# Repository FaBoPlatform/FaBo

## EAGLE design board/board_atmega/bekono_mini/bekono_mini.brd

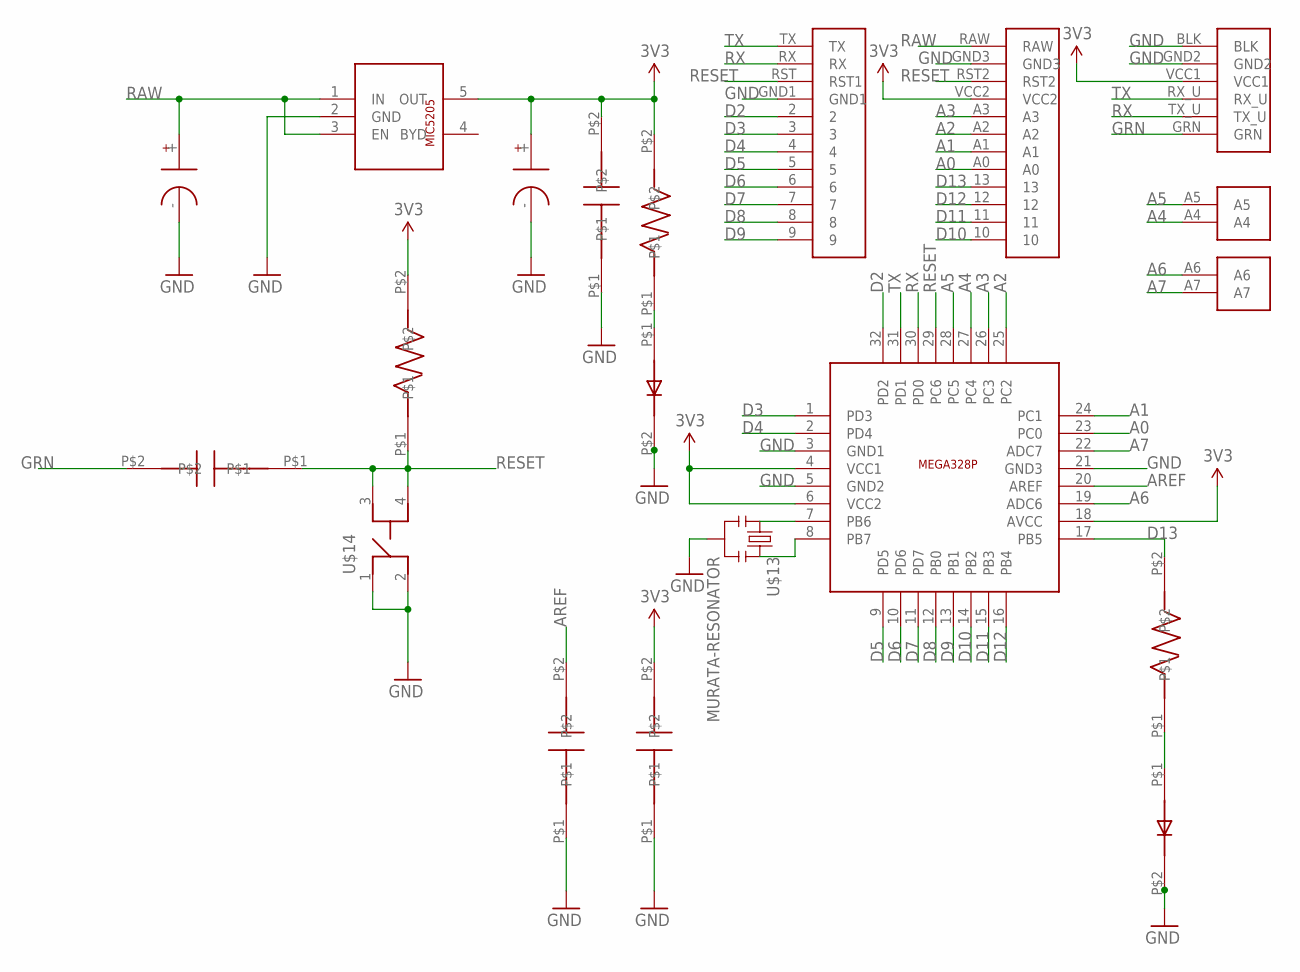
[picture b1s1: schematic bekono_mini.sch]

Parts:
U$1: ARDUIN-MINIPRO-BASE; ARDUINO-MINIPRO-BASE
U$2: MICREL-MIC5205
U$3, U$4: TANTALUM-CAPACITOR-1206
U$5, U$11, U$12, U$16: CAPACITOR-0603; 0603
U$6, U$9, U$15: RESISTOR-0603; 0603
U$7, U$10: LED-0603; 0603
U$8: ATMEL-MEGA328P; ATNEL-MEGA328P
U$13: MURATA-RESONATOR
U$14: SWITCH-LS6J2M-T

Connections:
3V3: U$1.VCC1, U$1.VCC2, U$2.5 (OUT), U$4.+, U$5.P$2, U$6.P$2, U$8.4 (VCC1), U$8.6 (VCC2), U$8.18 (AVCC), U$11.P$2, U$15.P$2
A0: U$1.A0, U$8.23 (PC0)
A1: U$1.A1, U$8.24 (PC1)
A2: U$1.A2, U$8.25 (PC2)
A3: U$1.A3, U$8.26 (PC3)
A4: U$1.A4, U$8.27 (PC4)
A5: U$1.A5, U$8.28 (PC5)
A6: U$1.A6, U$8.19 (ADC6)
A7: U$1.A7, U$8.22 (ADC7)
AREF: U$8.20 (AREF), U$12.P$2
D2: U$1.2, U$8.32 (PD2)
D3: U$1.3, U$8.1 (PD3)
D4: U$1.4, U$8.2 (PD4)
D5: U$1.5, U$8.9 (PD5)
D6: U$1.6, U$8.10 (PD6)
D7: U$1.7, U$8.11 (PD7)
D8: U$1.8, U$8.12 (PB0)
D9: U$1.9, U$8.13 (PB1)
D10: U$1.10, U$8.14 (PB2)
D11: U$1.11, U$8.15 (PB3)
D12: U$1.12, U$8.16 (PB4)
D13: U$1.13, U$8.17 (PB5), U$9.P$2
GND: U$1.BLK, U$1.GND1, U$1.GND2, U$1.GND3, U$2.2 (GND), U$3.-, U$4.-, U$5.P$1, U$7.P$2, U$8.3 (GND1), U$8.5 (GND2), U$8.21 (GND3), U$10.P$2, U$11.P$1, U$12.P$1, U$13.2, U$14.1, U$14.2
GRN: U$1.GRN, U$16.P$2
unnamed: U$6.P$1, U$7.P$1
unnamed: U$8.7 (PB6), U$13.1
unnamed: U$9.P$1, U$10.P$1
unnamed: U$8.8 (PB7), U$13.3
RAW: U$1.RAW, U$2.1 (IN), U$2.3 (EN), U$3.+
RESET: U$1.RST (RST1), U$1.RST2, U$8.29 (PC6), U$14.3, U$14.4, U$15.P$1, U$16.P$1
RX: U$1.RX, U$1.TX_U, U$8.30 (PD0)
TX: U$1.RX_U, U$1.TX, U$8.31 (PD1)

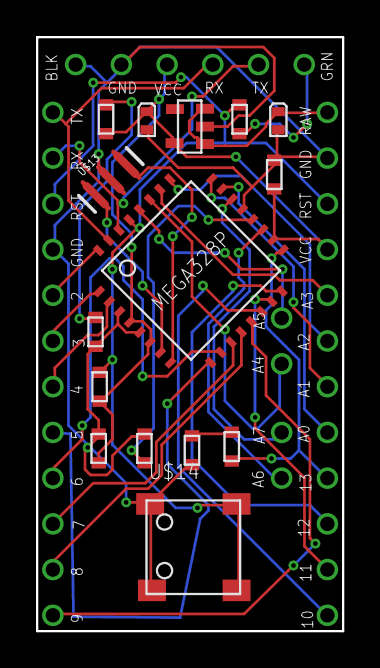
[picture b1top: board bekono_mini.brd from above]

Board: 2 copper layers, 17.0 x 33.0 mm, 16 parts (0 on the bottom side), 32 nets.

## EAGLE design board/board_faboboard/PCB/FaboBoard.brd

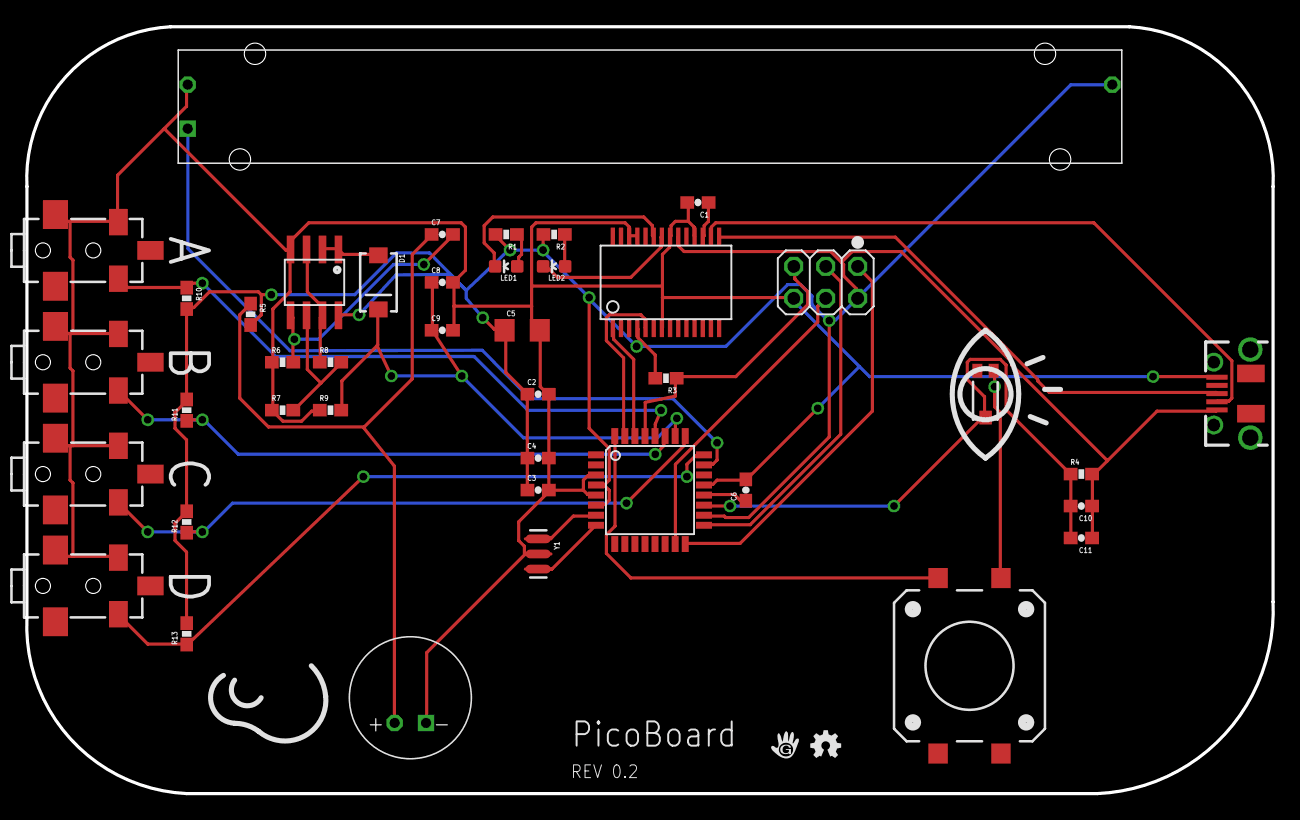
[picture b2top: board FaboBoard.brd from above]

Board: 2 copper layers, 99.1 x 61.0 mm, 43 parts (0 on the bottom side), 31 nets.

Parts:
C1, C2, C3, C4, C6, C7, C8, C9, C11: 0.1uF; EIA0603-CAP
C5: 10uF; EIA1206
C10: 0.22uF; EIA0603-CAP
D1: MBRA140; DIODE-SMA
JP1: AVR Prog.; 2X03
JPA: 2.5MM; STEREOJACK_2.5MM_SMD
JPB: 2.5MM; STEREOJACK_2.5MM_SMD
JPC: 2.5MM; STEREOJACK_2.5MM_SMD
JPD: 2.5MM; STEREOJACK_2.5MM_SMD
LED1: Red; EIA0603-LED
LED2: Green; EIA0603-LED
R1, R2: 1k; EIA0603-RES
R3, R5, R6, R10, R11, R12, R13: 10k; EIA0603-RES
R4, R8, R9: 100k; EIA0603-RES
R7: 2.2k; EIA0603-RES
R14: SLIDER; SLIDER_60MM
S1: TACT-SMD-12MM-TL3300CF160Q
U1: FT232RL; SSOP28
U2: ATMEGA328P-AU; TQFP-32-08
U7: TEMT6000
U8: LMV358; SO8-OP
U9: MIC9.7MM; MIC-ECM
U$2: LOGO_GCLUE
U$3: LOGO_OSHW_S
USB1: USBMICRO_SMD; USB_B_MICRO
Y1: 16MHz; RESONATOR_SMD

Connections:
3V3: C1.1, U1.17
5V: C2.1, C3.1, C4.1, C5.1, C10.1, C11.1, JP1.2, R1.2, R2.2, R3.2, R4.2, R5.2, R10.2, R11.2, R12.2, R13.2, R14.3, U1.4, U1.20, U2.4, U2.6, U2.18, U8.8, USB1.VBUS
GND: C1.2, C2.2, C3.2, C4.2, C5.2, C6.2, C8.2, C9.2, JP1.6, JPA.1, JPA.5, JPB.1, JPB.5, JPC.1, JPC.5, JPD.1, JPD.5, R6.1, R7.1, R9.1, R14.1, S1.4, U1.7, U1.18, U1.21, U1.25, U1.26, U2.3, U2.5, U2.21, U7.EMITTER, U8.4, U9.-, USB1.GND, Y1.2
LIGHT: C10.2, C11.2, R4.1, U2.19, U7.COLLECTOR
MISO: JP1.1, U2.16
MOSI: JP1.4, U2.15
unnamed: LED1.A, R1.1
unnamed: LED2.A, R2.1
unnamed: R7.2, R8.2, U8.6
unnamed: U2.7, Y1.1
unnamed: U2.8, Y1.3
unnamed: C6.1, U2.20
unnamed: S1.2, U2.32
unnamed: C7.1, R5.1, U9.+
unnamed: R14.2, U2.23
unnamed: C7.2, R6.2, U8.5
unnamed: D1.A, U8.1, U8.2
unnamed: R8.1, U8.3, U8.7
RA: JPA.4, R10.1, U2.28
RB: JPB.4, R11.1, U2.27
RC: JPC.4, R12.1, U2.25
RD: JPD.4, R13.1, U2.24
RES: JP1.5, R3.1, U2.29
RXI: U1.1, U2.30
RXLED: LED2.C, U1.22
SCK: JP1.3, U2.17
SOUND: C8.1, C9.1, D1.C, R9.2, U2.26
TXLED: LED1.C, U1.23
TXO: U1.5, U2.31
USB_D+: U1.15, USB1.D+
USB_D-: U1.16, USB1.D-

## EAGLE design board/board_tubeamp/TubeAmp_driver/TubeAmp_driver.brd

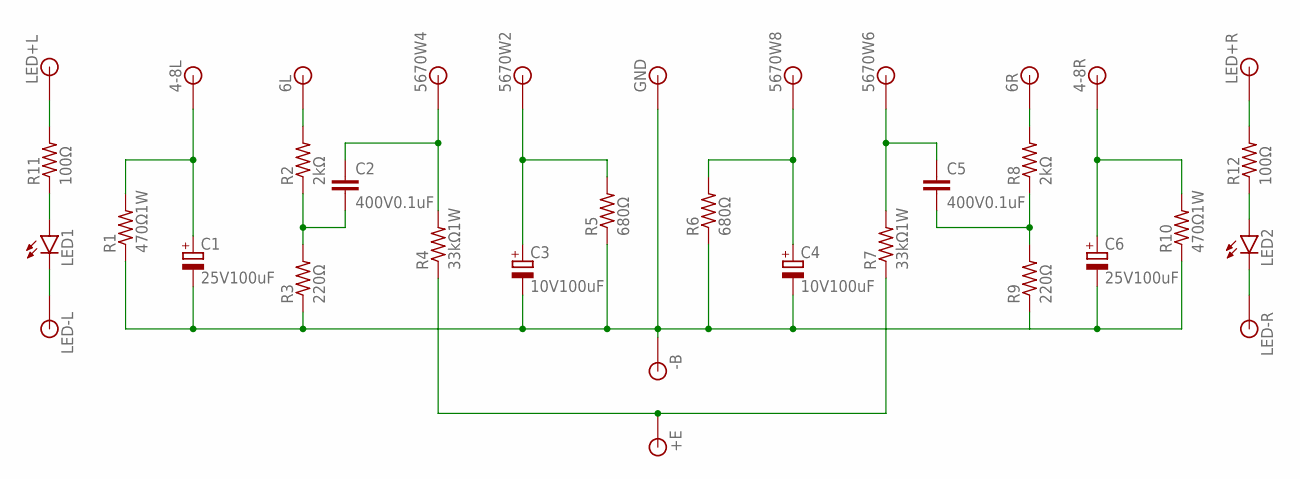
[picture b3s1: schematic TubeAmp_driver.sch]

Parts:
4-8L, 4-8R, 6L, 6R, 5670W2, 5670W4, 5670W6, 5670W8: PIN-1X11.2MM; PIN-1X1_1.2MM
+E: PIN-1X11.2MM; PIN-1X1_1.2MM
-B: PIN-1X11.2MM; PIN-1X1_1.2MM
C1, C6: 25V100uF; CPOL25_65
C2, C5: 400V0.1uF; C125_63X155
C3, C4: 10V100uF; CPOL25_65
GND: PIN-1X11.2MM; PIN-1X1_1.2MM
LED1, LED2: LED-3MM
LED+L: PIN-1X11.2MM; PIN-1X1_1.2MM
LED+R: PIN-1X11.2MM; PIN-1X1_1.2MM
LED-L: PIN-1X11.2MM; PIN-1X1_1.2MM
LED-R: PIN-1X11.2MM; PIN-1X1_1.2MM
R1, R10: 470Ω1W; RESISTOR_1W
R2, R8: 2kΩ; RESISTOR_1/4W
R3, R9: 220Ω; RESISTOR_1/4W
R4, R7: 33kΩ1W; RESISTOR_1W
R5, R6: 680Ω; RESISTOR_1/4W
R11, R12: 100Ω; RESISTOR_1/4W

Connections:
4-8L: 4-8L.1, C1.+, R1.2
4-8R: 4-8R.1, C6.+, R10.2
6L: 6L.1, R2.2
6R: 6R.1, R8.2
5670W2: 5670W2.1, C3.+, R5.2
5670W4: 5670W4.1, C2.1, R4.2
5670W6: 5670W6.1, C5.1, R7.2
5670W8: 5670W8.1, C4.+, R6.2
+E: +E.1, R4.1, R7.1
-B: -B.1, C1.-, C3.-, C4.-, C6.-, GND.1, R1.1, R3.1, R5.1, R6.1, R9.1, R10.1
LED+L: LED+L.1, R11.2
LED+R: LED+R.1, R12.2
LED-L: LED1.K (C), LED-L.1
LED-R: LED2.K (C), LED-R.1
unnamed: C2.2, R2.1, R3.2
unnamed: LED1.A, R11.1
unnamed: LED2.A, R12.1
unnamed: C5.2, R8.1, R9.2

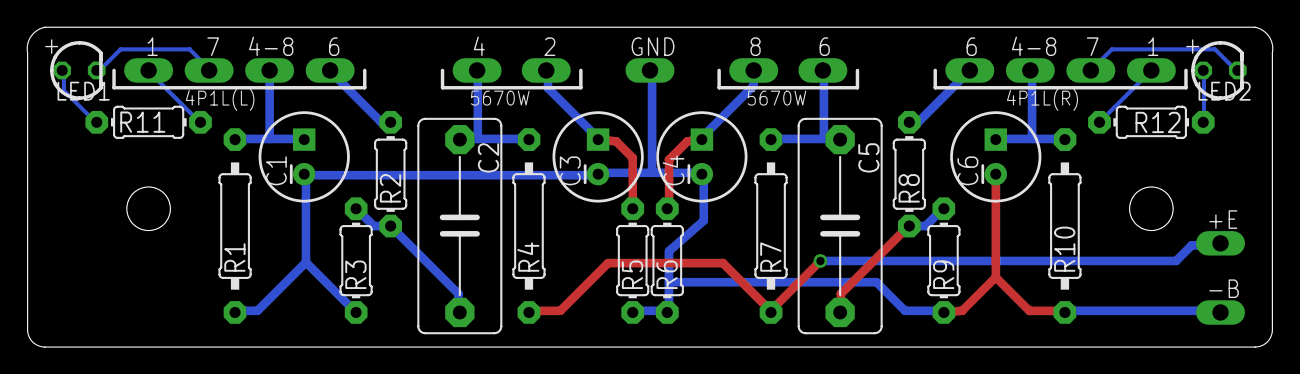
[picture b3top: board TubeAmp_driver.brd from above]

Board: 2 copper layers, 91.5 x 23.5 mm, 35 parts (0 on the bottom side), 18 nets.

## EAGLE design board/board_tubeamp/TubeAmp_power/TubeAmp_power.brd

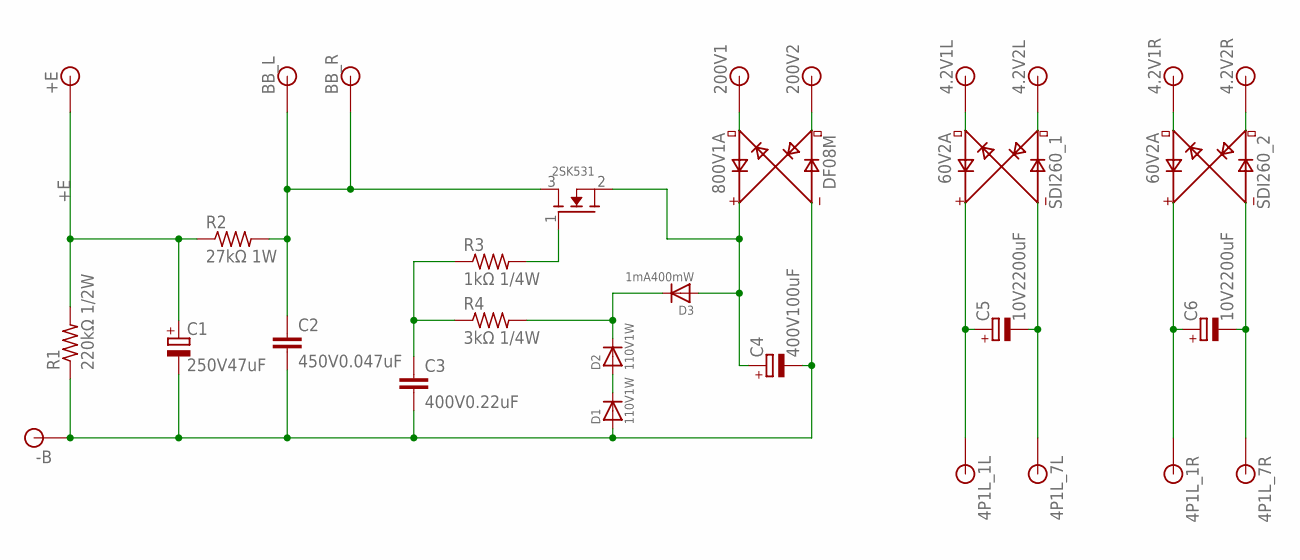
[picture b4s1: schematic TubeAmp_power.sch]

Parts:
2SK531: MOSFET_N
4.2V1L, 4.2V1R, 4.2V2L, 4.2V2R, 4P1L_1L, 4P1L_1R, 4P1L_7L, 4P1L_7R, 200V1, 200V2: PIN-1X11.2MM; PIN-1X1_1.2MM
+E: PIN-1X11.2MM; PIN-1X1_1.2MM
-B: PIN-1X11.2MM; PIN-1X1_1.2MM
BB_L: PIN-1X11.2MM; PIN-1X1_1.2MM
BB_R: PIN-1X11.2MM; PIN-1X1_1.2MM
C1: 250V47uF; CPOL50_90
C2: 450V0.047uF; C150_63X200
C3: 400V0.22uF; C100_63X130
C4: 400V100uF; CPOL75_150
C5, C6: 10V2200uF; CPOL50_90
D1, D2: 110V1W; DIODE_63
D3: 1mA400mW; DIODE_63
DF08M: 800V1A; RECTIFIER
R1: 220kΩ 1/2W; RESISTOR_1/2W
R2: 27kΩ 1W; RESISTOR_1W
R3: 1kΩ 1/4W; RESISTOR_1/4W
R4: 3kΩ 1/4W; RESISTOR_1/4W
SDI260_1, SDI260_2: 60V2A; RECTIFIER

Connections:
4.2V1L: 4.2V1L.1, SDI260_1.AC2
4.2V1R: 4.2V1R.1, SDI260_2.AC2
4.2V2L: 4.2V2L.1, SDI260_1.AC1
4.2V2R: 4.2V2R.1, SDI260_2.AC1
4P1L_1L: 4P1L_1L.1, C5.+, SDI260_1.+
4P1L_1R: 4P1L_1R.1, C6.+, SDI260_2.+
4P1L_7L: 4P1L_7L.1, C5.-, SDI260_1.-
4P1L_7R: 4P1L_7R.1, C6.-, SDI260_2.-
200V1: 200V1.1, DF08M.AC2
200V2: 200V2.1, DF08M.AC1
+E: +E.1, C1.+, R1.2, R2.1
BB: 2SK531.3 (D), BB_L.1, BB_R.1, C2.1, R2.2
GND: -B.1, C1.-, C2.2, C3.2, C4.-, D1.A, DF08M.-, R1.1
unnamed: 2SK531.1 (G), R3.2
unnamed: 2SK531.2 (S), C4.+, D3.A, DF08M.+
unnamed: C3.1, R3.1, R4.1
unnamed: D2.K, D3.K, R4.2
unnamed: D1.K, D2.A

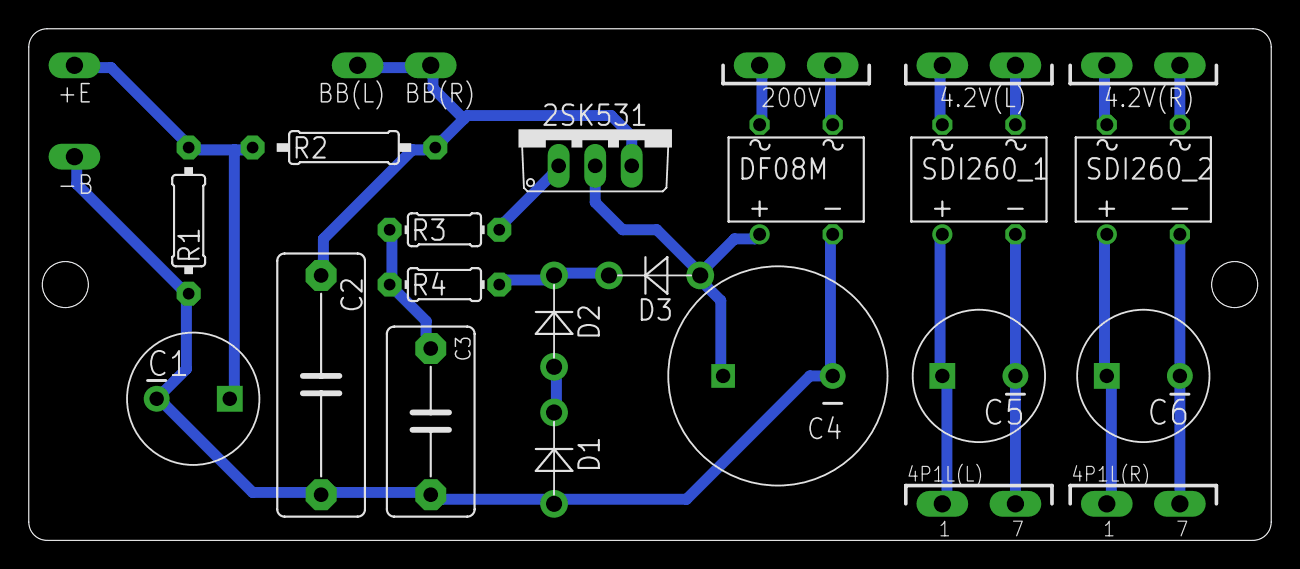
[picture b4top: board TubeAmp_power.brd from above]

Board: 2 copper layers, 86.4 x 35.6 mm, 31 parts (1 on the bottom side), 18 nets.

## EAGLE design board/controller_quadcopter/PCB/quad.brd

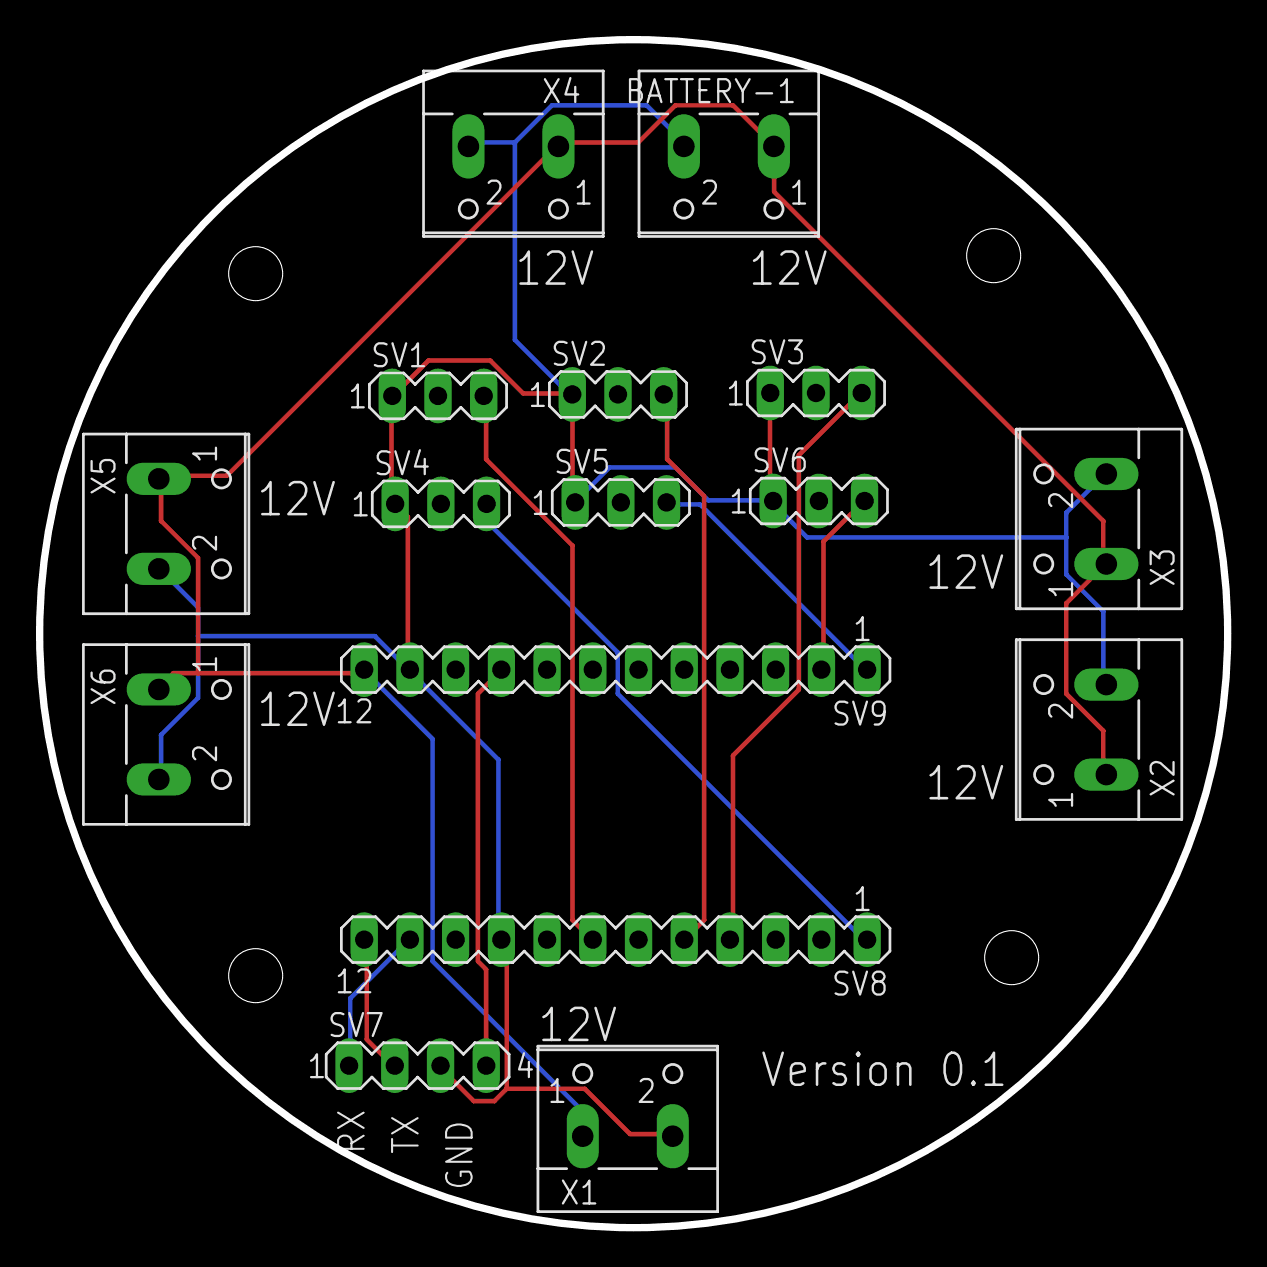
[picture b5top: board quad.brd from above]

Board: 2 copper layers, 66.0 x 66.0 mm, 16 parts (0 on the bottom side), 11 nets.

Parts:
BATTERY-1: W237-102
SV1, SV2, SV3, SV4, SV5, SV6: MA03-1
SV7: MA04-1
SV8, SV9: MA12-1
X1, X2, X3, X4, X5, X6: W237-102

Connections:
+5V: SV7.4, SV9.9
+12V: BATTERY-1.1, SV9.12, X1.1, X2.1, X3.1, X4.1, X5.1, X6.1
GND: BATTERY-1.2, SV1.1, SV2.1, SV3.1, SV4.1, SV5.1, SV6.1, SV7.3, SV8.9, SV9.11, X1.2, X2.2, X3.2, X4.2, X5.2, X6.2
M1: SV1.3, SV8.7
M2: SV2.3, SV8.5
M3: SV3.3, SV8.4
M4: SV4.3, SV8.1
M5: SV5.3, SV9.1
M6: SV6.3, SV9.2
RX: SV7.1, SV8.11
TX: SV7.2, SV8.12

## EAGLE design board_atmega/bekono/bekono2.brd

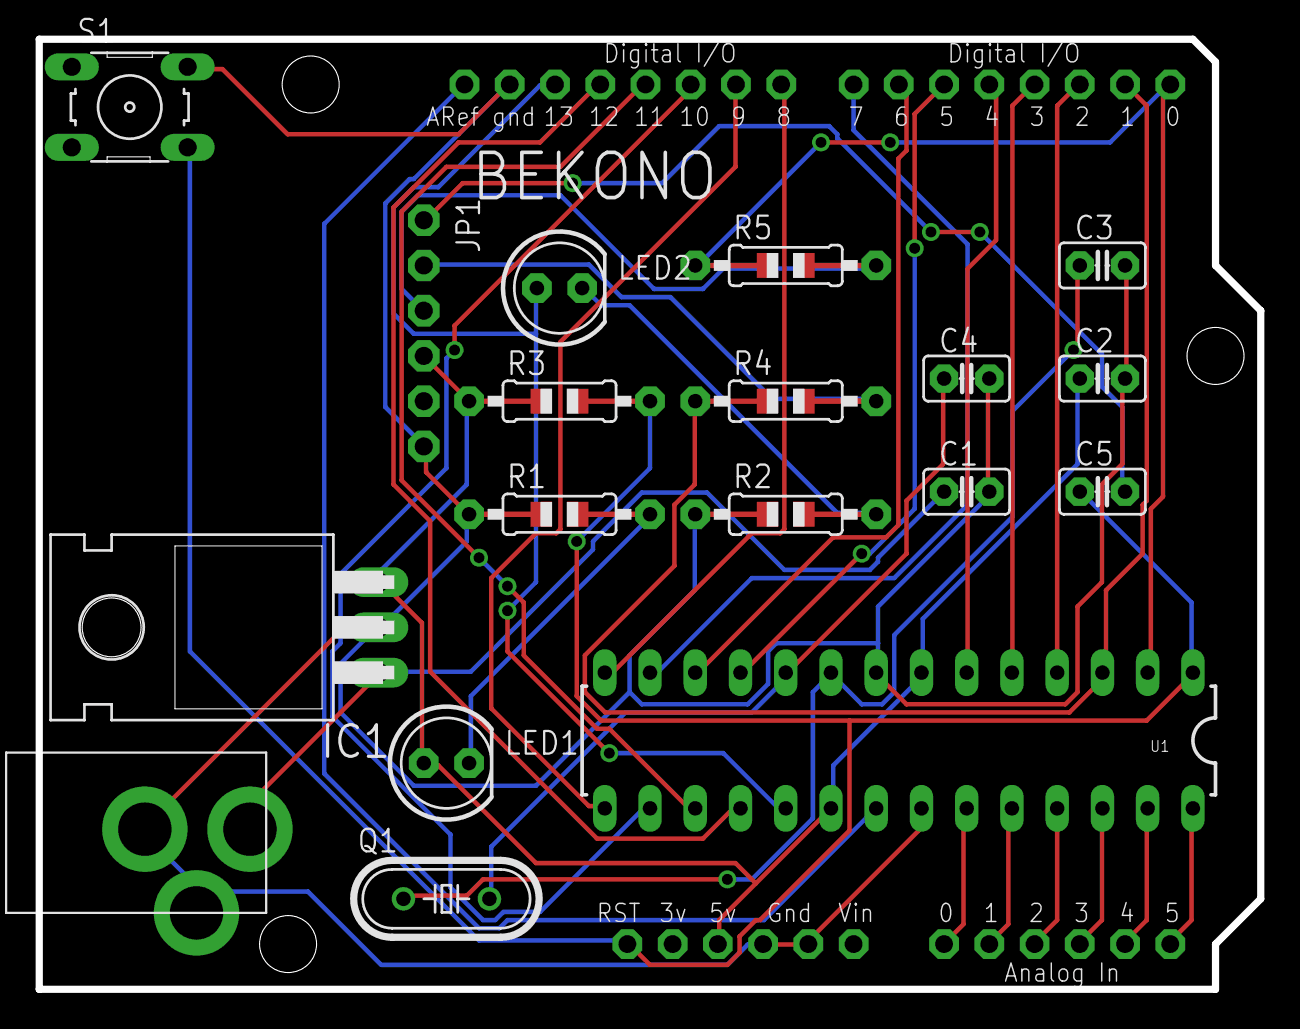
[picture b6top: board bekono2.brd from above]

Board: 2 copper layers, 68.6 x 53.3 mm, 19 parts (0 on the bottom side), 32 nets.

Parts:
C1: 0.1uf; C2.5-2
C2: 0.33uf; C2.5-2
C3, C4: 33pf; C2.5-2
C5: 1uf; C2.5-2
IC1: 7805T; TO220H
JP1: 1X06-CLEANBIG
LED1, LED2: LED5MM
Q1: HC49/S
R1, R2: 330; 0805-THM
R3: 10K; 0805-THM
R4, R5: 1K; 0805-THM
S1: B3F-10XX
U1: ATMEGA328P_PDIP; DIL28-3
U$1: ARDUINO-BPLACE
U$2: 2.1MMJACKTHM; PJ-102A

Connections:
+5V: C2.1, IC1.3, JP1.4, LED1.A, R3.1, U1.7, U1.20, U$1.5V
AREF: U1.21, U$1.AREF
GND: C1.2, C2.2, C3.2, C4.2, IC1.2, JP1.6, R1.1, R2.1, S1.2, U1.8, U1.22, U$1.GND, U$1.GND1, U$1.GND2, U$2.RING, U$2.RING_SW
unnamed: C1.1, IC1.1, U$2.TIP
unnamed: LED1.K, R1.2
unnamed: LED2.K, R2.2
unnamed: C5.2, JP1.1
unnamed: JP1.2, R4.2
unnamed: JP1.3, R5.2
PB0: U1.14, U$1.D8
PB1: U1.15, U$1.D9
PB2: U1.16, U$1.D10
PB3: U1.17, U$1.D11
PB4: U1.18, U$1.D12
PB5: LED2.A, U1.19, U$1.D13
PB6: C3.1, Q1.1, U1.9
PB7: C4.1, Q1.2, U1.10
PC0: U1.23, U$1.A0
PC1: U1.24, U$1.A1
PC2: U1.25, U$1.A2
PC3: U1.26, U$1.A3
PC4: U1.27, U$1.A4
PC5: U1.28, U$1.A5
PC6: C5.1, R3.2, S1.4, U1.1, U$1.RESET
PD0: R5.1, U1.2, U$1.D0
PD1: R4.1, U1.3, U$1.D1
PD2: U1.4, U$1.D2
PD3: U1.5, U$1.D3
PD4: U1.6, U$1.D4
PD5: U1.11, U$1.D5
PD6: U1.12, U$1.D6
PD7: U1.13, U$1.D7

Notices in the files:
parts and their libraries:
SparkFun-DigitalIC: Licensing: Creative Commons ShareAlike 4.0 International - https://creativecommons.org/licenses/by-sa/4.0
